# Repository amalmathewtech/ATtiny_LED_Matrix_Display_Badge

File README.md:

# ATtiny_LED_Matrix_Display_Badge
An ATtiny85 based badge size PCB that can display alphabets and numbers .

Project Details: https://www.hackster.io/amalmathewtech/attiny-led-matrix-display-badge-f2c664

[url](https://twitter.com/Hacksterio/status/1091351536943415298)

[url](https://twitter.com/amalmathewtech/status/1158927944246366209)

[url](https://twitter.com/MicrochipMakes/status/1091068308395307015)

[url](https://twitter.com/MicrochipMakes/status/1305969818621882375)

Made With ❤ in OpenSource

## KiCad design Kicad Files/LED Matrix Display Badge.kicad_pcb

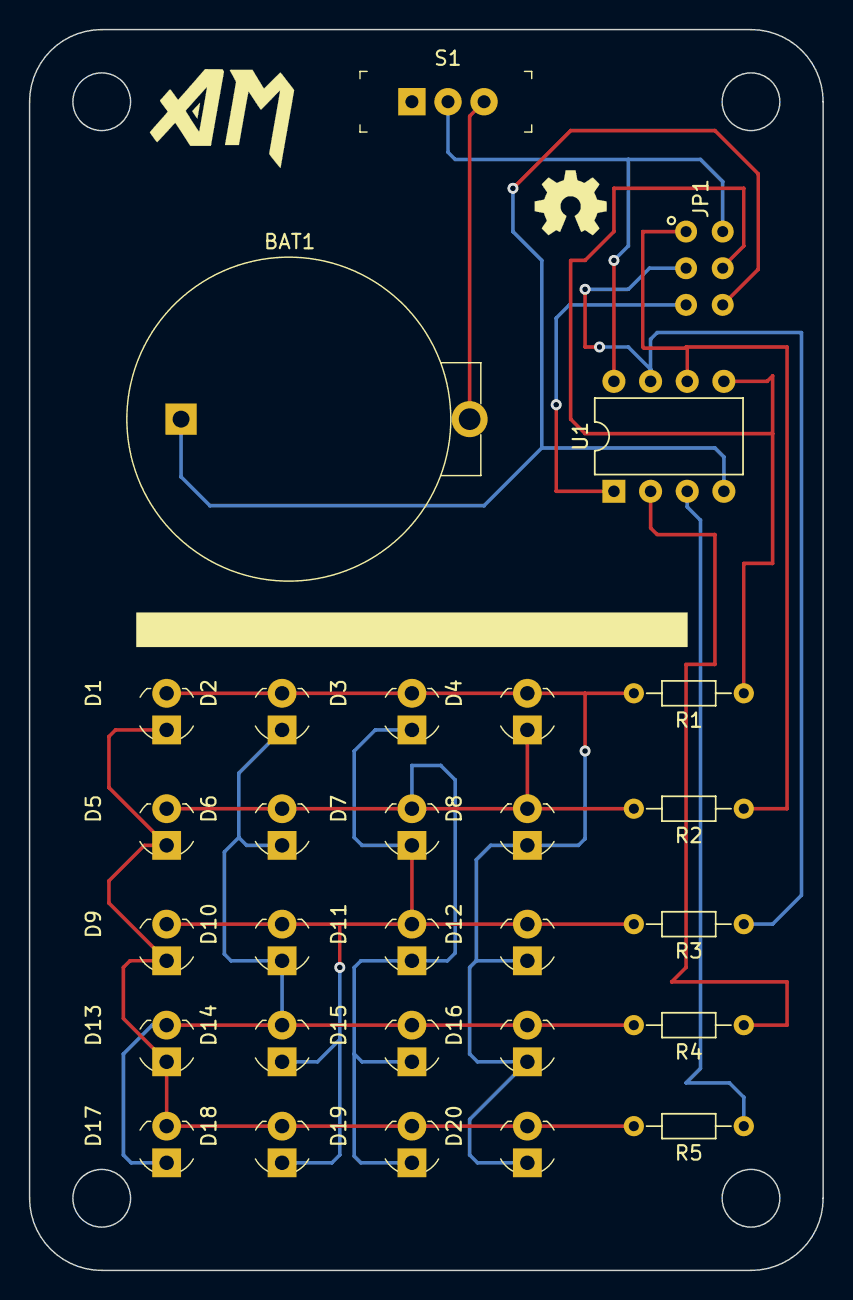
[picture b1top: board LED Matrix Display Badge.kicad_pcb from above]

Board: 2 copper layers, 55.0 x 86.0 mm, 29 parts (0 on the bottom side), 14 nets.

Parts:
BAT1: BS-7; Battery_Holder_Coin_2032_BS-7
D1, D2, D3, D4, D5, D6, D7, D8, D9, D10, D11, D12, D13, D14, D15, D16, D17, D18, D19, D20: LED; LED_3mm_Radial
JP1: 6pinconnector; 6PINCONNECTOR
R1, R2, R3, R4, R5: 100; R_Axial_DIN0204_L3.6mm_D1.6mm_P7.62mm_Horizontal
S1: EG1218; Switch_Slide_11.6x4mm_EG1218
U1: ATTINY85-20PU; DIP-8_W7.62mm

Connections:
GND: BAT1.Neg, JP1.6, U1.4
MISO: JP1.1, R2.1, U1.6
MOSI: JP1.4, R1.1, U1.5
unnamed: BAT1.Pos, S1.3
unnamed: D1.1, D5.1, D9.1, D13.1, D17.2, D18.2, D19.2, D20.2, R5.2
unnamed: D1.2, D2.2, D3.2, D4.2, D8.1, D12.1, D16.1, D20.1, R1.2
unnamed: D2.1, D6.1, D10.1, D13.2, D14.2, D15.2, D16.2, D17.1, R4.2
unnamed: D3.1, D7.1, D9.2, D10.2, D11.2, D12.2, D14.1, D18.1, R3.2
unnamed: D4.1, D5.2, D6.2, D7.2, D8.2, D11.1, D15.1, D19.1, R2.2
PB3: R4.1, U1.2
PB4: R5.1, U1.3
RST: JP1.5, U1.1
SCK: JP1.3, R3.1, U1.7
VCC: JP1.2, S1.2, U1.8

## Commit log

2019-02-23 Create LICENSE

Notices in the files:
Kicad Files/LED Matrix Display Badge.kicad_pcb:
License: CC BY 4.0
